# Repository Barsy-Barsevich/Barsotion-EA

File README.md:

# Barsotion GBK EpsilonAnomalain
Board computer for model rockets, the 10th board after Berkut

## ⚡️Manual
- [EA&TA_user_manual_revD.pdf (newest revision)](https://github.com/Barsy-Barsevich/Barsotion-TA/blob/main/Manual/EA%26TA_user_manual_revD.pdf)
- [EA&TA_user_manual_revC.pdf](https://github.com/Barsy-Barsevich/Barsotion-TA/blob/main/Manual/EA&TA_user_manual_revC.pdf)
- [EA&TA_user_manual_preliminary_edition_revB.pdf](https://github.com/Barsy-Barsevich/Barsotion-TA/blob/main/Manual/EA&TA_user_manual_preliminary_edition_revB.pdf)
- [EA&TA_user_manual_preliminary_edition_revA.pdf](https://github.com/Barsy-Barsevich/Barsotion-TA/blob/main/Manual/EA&TA_user_manual_preliminary_edition_revA.pdf)

## ⚡️Software
- [EA/TA software packet](https://github.com/Barsy-Barsevich/Barsotion-xA-software)

## ⚡️Continious progress
- [Previous version: Barsotion GBK DeltaAnomalain](https://github.com/Barsy-Barsevich/Barsotion-GBK-DeltaAnomalain)
- [Next version: Barsotion-TA (ThetaAnomalain)](https://github.com/Barsy-Barsevich/Barsotion-TA)

## ⚡️Schematic

## ⚡️Parameters
- Microcontroller: ESP32-S3FN8 (2x Xtensa LX7 core)
- Clock frequency: 240MHz
- Gyroscope: on-board ICM-42688-P (SPI, interrupt channel)
- Barometer: on-board, BMP388 (I2C)
- Hygrometer: on-board, AHT20 (I2C)
- Memory: 1Gbit SPI NAND Flash W25N04GVZEIG (Quad SPI)

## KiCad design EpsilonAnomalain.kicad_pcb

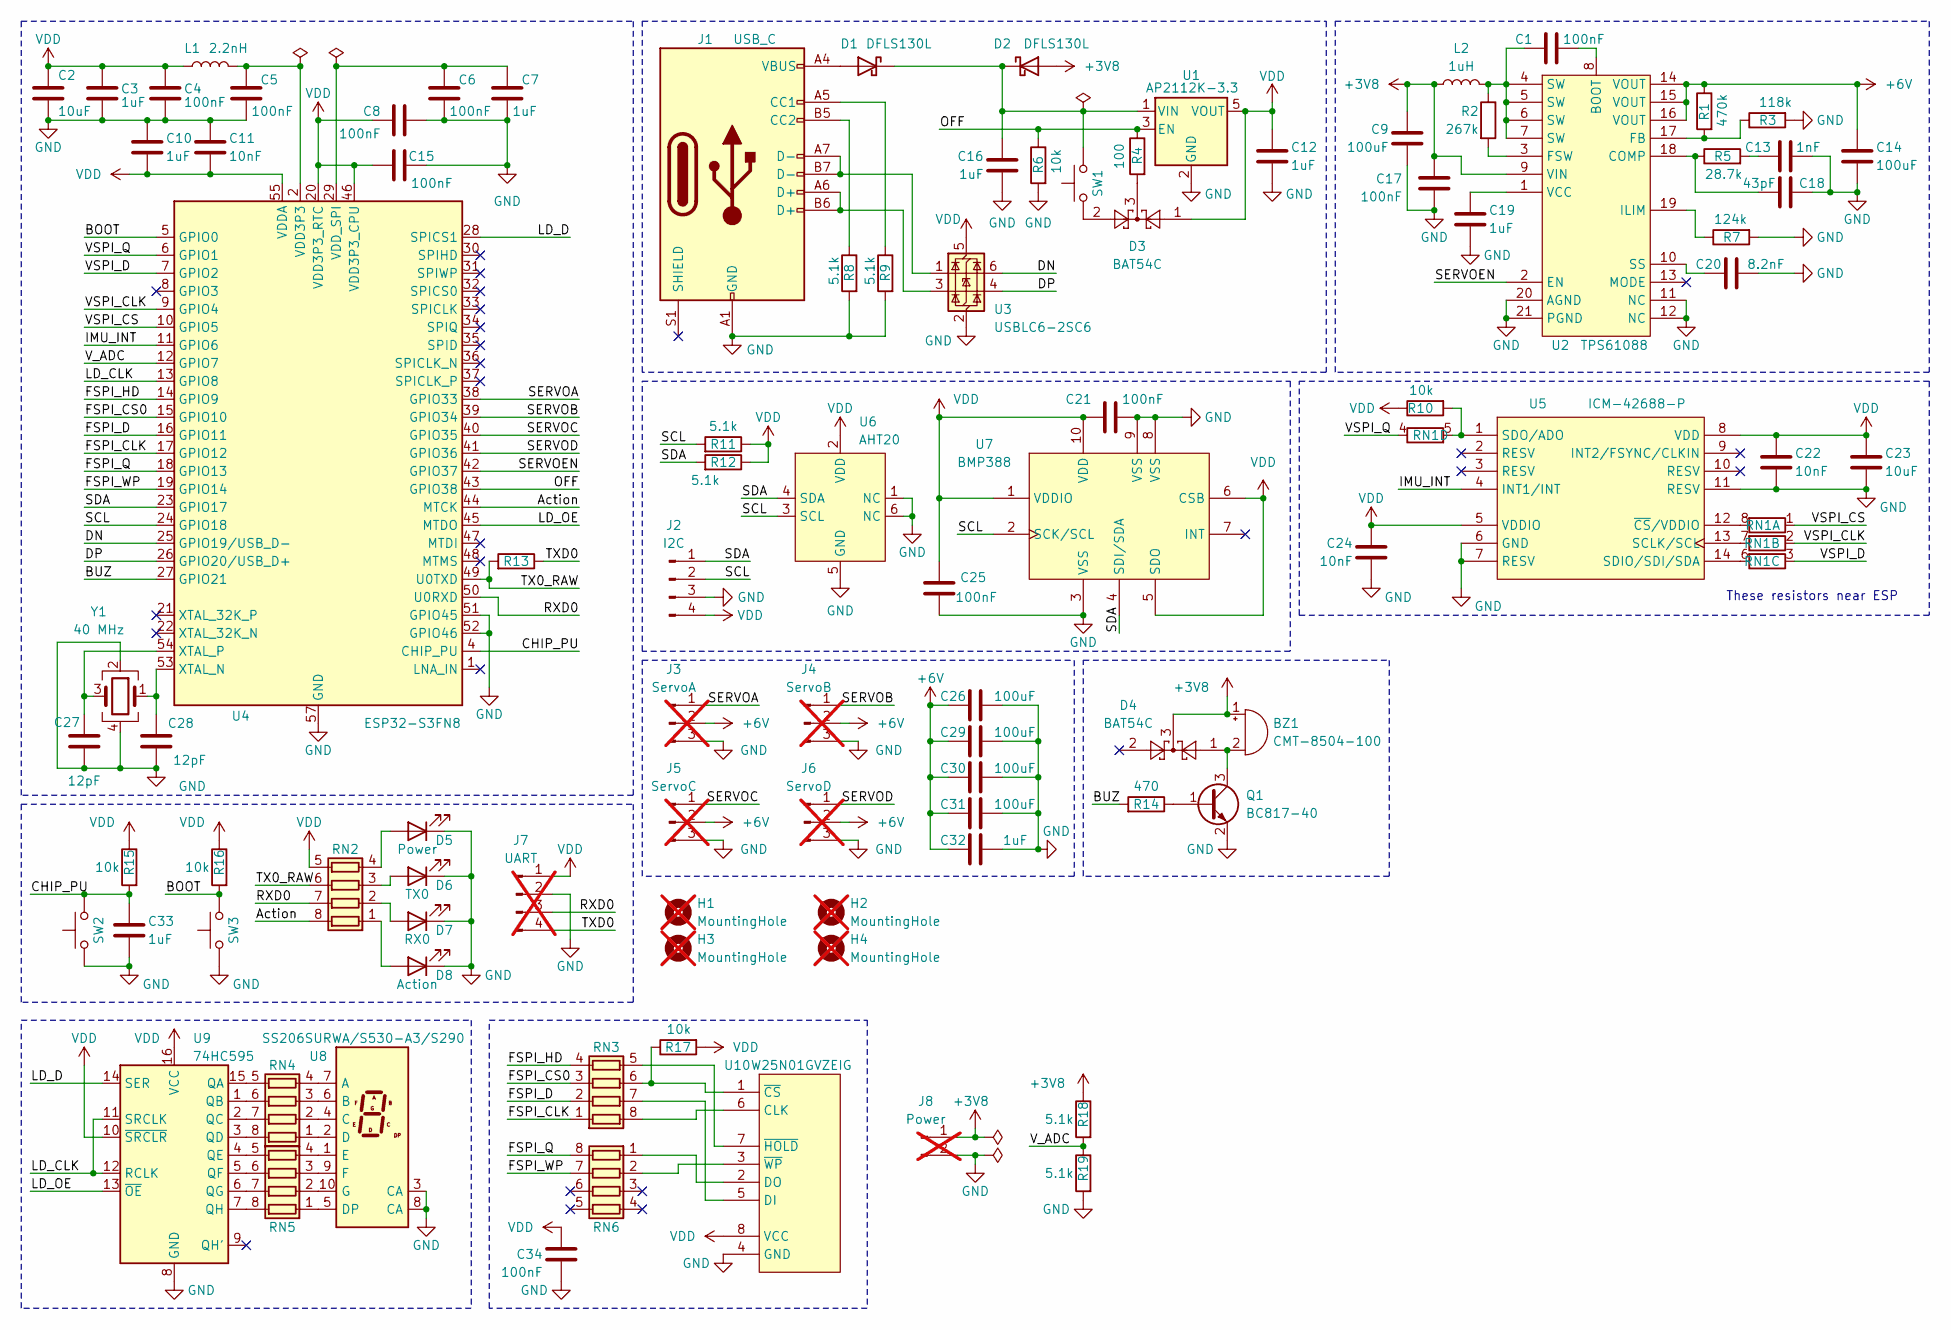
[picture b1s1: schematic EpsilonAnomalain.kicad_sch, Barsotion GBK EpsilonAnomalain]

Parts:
BZ1: CMT-8504-100; MagneticBuzzer_CUI_CMT-8504-100-SMT; Mfr.Part CMT-8504-100
C1, C4, C5, C6, C8, C15, C17, C21, C25, C34: 100nF; C_0402_1005Metric
C2, C23: 10uF; C_0402_1005Metric
C3, C7, C10, C12, C16, C19, C32, C33: 1uF; C_0402_1005Metric
C9, C14, C26, C29, C30, C31: 100uF; C_1206_3216Metric
C11, C22, C24: 10nF; C_0402_1005Metric
C13: 1nF; C_0402_1005Metric
C18: 43pF; C_0402_1005Metric
C20: 8.2nF; C_0402_1005Metric
C27, C28: 12pF; C_0402_1005Metric
D1, D2: DFLS130L; D_PowerDI-123
D3, D4: BAT54C; SOT-23
D5: Power; LED_0603_1608Metric
D6: TX0; LED_0603_1608Metric
D7: RX0; LED_0603_1608Metric
D8: Action; LED_0603_1608Metric
H1, H2, H3, H4: MountingHole; MountingHole_3.2mm_M3_Pad_Via; not fitted
J1: USB_C; USB_C_Receptacle_GCT_USB4105-xx-A_16P_TopMnt_Horizontal; Mfr.Part TYPE C-DB-116PWB
J2: I2C; JST_GH_SM04B-GHS-TB_1x04-1MP_P1.25mm_Horizontal; Mfr.Part A1257WR-S-4P
J3: ServoA; JST_XH_B3B-XH-A_1x03_P2.50mm_Vertical; not fitted
J4: ServoB; JST_XH_B3B-XH-A_1x03_P2.50mm_Vertical; not fitted
J5: ServoC; JST_XH_B3B-XH-A_1x03_P2.50mm_Vertical; not fitted
J6: ServoD; JST_XH_B3B-XH-A_1x03_P2.50mm_Vertical; not fitted
J7: UART; JST_XH_B4B-XH-A_1x04_P2.50mm_Vertical; not fitted
J8: Power; Battery_3V7_Cable_connector_v2; not fitted
L1: 2.2nH; L_0402_1005Metric
L2: 1uH; L_APV_APH0630; Mfr.Part APH0630T1R0M
Q1: BC817-40; SOT-23
R1: 470k; R_0402_1005Metric
R2: 267k; R_0402_1005Metric
R3: 118k; R_0402_1005Metric
R4: 100; R_0402_1005Metric
R5: 28.7k; R_0402_1005Metric
R6, R10, R15, R16, R17: 10k; R_0402_1005Metric
R7: 124k; R_0402_1005Metric
R8, R9, R11, R12, R18, R19: 5.1k; R_0402_1005Metric
R13, R14: 470; R_0402_1005Metric
RN1: 47; R_Array_Convex_4x0402
RN2, RN4, RN5: 1k; R_Array_Convex_4x0402
RN3, RN6: 0; R_Array_Convex_4x0402
SW1, SW2, SW3: TS-1187A-B-A-B; SW_SPST_TL3342; Mfr.Part TS-1187A-B-A-B
U1: AP2112K-3.3; SOT-23-5; Mfr.Part AP2112K-3.3
U2: TPS61088; RHL0020A; Mfr.Part TPS61088
U3: USBLC6-2SC6; SOT-23-6; Mfr.Part USBLC6-2SC6
U4: ESP32-S3FN8; QFN-56-1EP_7x7mm_P0.4mm_EP4x4mm; Mfr.Part ESP32-S3FN8
U5: ICM-42688-P; LGA-14_3x2.5mm_P0.5mm_LayoutBorder3x4y; Mfr.Part ICM-42688-P
U6: AHT20; Mfr.Part AHT20
U7: BMP388; BMP388_v2; Mfr.Part BMP388
U8: SS206SURWA/S530-A3/S290; SS206SURWA; Mfr.Part SS206SURWA/S530-A3/S290
U9: 74HC595; TSSOP-16_4.4x5mm_P0.65mm
U10: W25N01GVZEIG; WSON-8-1EP_8x6mm_P1.27mm_EP3.4x4.3mm; Mfr.Part W25N01GVZEIG
Y1: 40 MHz; Crystal_SMD_3225-4Pin_3.2x2.5mm

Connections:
+3V8: BZ1.1 (+), C9.1, C17.1, D2.2 (A), D4.3, J8.1, L2.1, R18.1, U2.9 (VIN)
+6V: C14.1, C26.1, C29.1, C30.1, C31.1, C32.1, J3.2, J4.2, J5.2, J6.2, R1.1, U2.14 (VOUT), U2.15 (VOUT), U2.16 (VOUT)
/Action: RN2.8 (R1.2), U4.44 (MTCK)
/BOOT: R16.2, SW3.2, U4.5 (GPIO0)
/BUZ: R14.2, U4.27 (GPIO21)
/CHIP_PU: C33.1, R15.2, SW2.2, U4.4 (CHIP_PU)
/DN: U3.6 (I/O1), U4.25 (GPIO19/USB_D-)
/DP: U3.4 (I/O2), U4.26 (GPIO20/USB_D+)
/FSPI_CLK: RN3.1 (R1.1), U4.17 (GPIO12)
/FSPI_CS0: RN3.3 (R3.1), U4.15 (GPIO10)
/FSPI_D: RN3.2 (R2.1), U4.16 (GPIO11)
/FSPI_HD: RN3.4 (R4.1), U4.14 (GPIO9)
/FSPI_Q: RN6.8 (R1.2), U4.18 (GPIO13)
/FSPI_WP: RN6.7 (R2.2), U4.19 (GPIO14)
/IMU_INT: U4.11 (GPIO6), U5.4 (INT1/INT)
/LD_CLK: U4.13 (GPIO8), U9.11 (SRCLK), U9.12 (RCLK)
/LD_D: U4.28 (SPICS1), U9.14 (SER)
/LD_OE: U4.45 (MTDO), U9.13 (~OE)
/OFF: R4.1, R6.1, U1.3 (EN), U4.43 (GPIO38)
/RXD0: J7.3, RN2.7 (R2.2), U4.50 (U0RXD)
/SCL: J2.2, R11.2, U4.24 (GPIO18), U6.3 (SCL), U7.2 (SCK/SCL)
/SDA: J2.1, R12.2, U4.23 (GPIO17), U6.4 (SDA), U7.4 (SDI/SDA)
/SERVOA: J3.1, U4.38 (GPIO33)
/SERVOB: J4.1, U4.39 (GPIO34)
/SERVOC: J5.1, U4.40 (GPIO35)
/SERVOD: J6.1, U4.41 (GPIO36)
/SERVOEN: U2.2 (EN), U4.42 (GPIO37)
/TX0_RAW: R13.2, RN2.6 (R3.2), U4.49 (U0TXD)
/TXD0: J7.4, R13.1
/VSPI_CLK: RN1.2 (R2.1), U4.9 (GPIO4)
/VSPI_CS: RN1.1 (R1.1), U4.10 (GPIO5)
/VSPI_D: RN1.3 (R3.1), U4.7 (GPIO2)
/VSPI_Q: RN1.4 (R4.1), U4.6 (GPIO1)
/V_ADC: R18.2, R19.1, U4.12 (GPIO7)
GND: C2.2, C3.2, C4.2, C5.2, C6.2, C7.2, C8.2, C9.2, C10.1, C11.1, C12.2, C13.1, C14.2, C15.2, C16.2, C17.2, C18.1, C19.2, C20.1, C21.2, C22.2, C23.2, C24.2, C25.1, C26.2, C27.2, C28.2, C29.2, C30.2, C31.2, C32.2, C33.2, C34.2, D5.1 (K), D6.1 (K), D7.1 (K), D8.1 (K), J1.A1 (GND), J1.A12 (GND), J1.B1 (GND), J1.B12 (GND), J2.3, J3.3, J4.3, J5.3, J6.3, J7.2, J8.2, Q1.2 (E), R3.2, R6.2, R7.2, R8.2, R9.2, R19.2, SW2.1, SW3.1, U1.2 (GND), U2.11 (NC), U2.12 (NC), U2.20 (AGND), U2.21 (PGND), U3.2 (GND), U4.51 (GPIO45), U4.52 (GPIO46), U4.57 (GND), U5.6 (GND), U5.7 (RESV), U5.11 (RESV), U6.1 (NC), U6.5 (GND), U6.6 (NC), U7.3 (VSS), U7.8 (VSS), U7.9 (VSS), U8.3 (CA), U8.8 (CA), U9.8 (GND), U10.4 (GND), Y1.2, Y1.4
unnamed: BZ1.2 (-), D4.1, Q1.3 (C)
unnamed: C1.2, L2.2, R2.1, U2.4 (SW), U2.5 (SW), U2.6 (SW), U2.7 (SW)
unnamed: C5.1, L1.2, U4.2 (VDD3P3), U4.3 (VDD3P3)
unnamed: C13.2, R5.2
unnamed: D1.2 (A), J1.A4 (VBUS), J1.A9 (VBUS), J1.B4 (VBUS), J1.B9 (VBUS)
unnamed: C16.1, D1.1 (K), D2.1 (K), SW1.2, U1.1 (VIN)
unnamed: D3.2, SW1.1
unnamed: D3.3, R4.2
unnamed: D5.2 (A), RN2.4 (R4.1)
unnamed: D6.2 (A), RN2.3 (R3.1)
unnamed: D7.2 (A), RN2.2 (R2.1)
unnamed: D8.2 (A), RN2.1 (R1.1)
unnamed: J1.A5 (CC1), R9.1
unnamed: J1.B5 (CC2), R8.1
unnamed: J1.A6 (D+), J1.B6 (D+), U3.3 (I/O2)
unnamed: J1.A7 (D-), J1.B7 (D-), U3.1 (I/O1)
unnamed: Q1.1 (B), R14.1
unnamed: RN1.8 (R1.2), U5.12 (~CS/VDDIO)
unnamed: RN1.7 (R2.2), U5.13 (SCLK/SCL)
unnamed: RN1.6 (R3.2), U5.14 (SDIO/SDI/SDA)
unnamed: R10.2, RN1.5 (R4.2), U5.1 (SDO/ADO)
unnamed: RN3.8 (R1.2), U10.6 (CLK)
unnamed: RN3.7 (R2.2), U10.5 (DI)
unnamed: R17.1, RN3.6 (R3.2), U10.1 (~CS)
unnamed: RN3.5 (R4.2), U10.7 (~HOLD)
unnamed: RN4.1 (R1.1), U8.2 (D)
unnamed: RN4.8 (R1.2), U9.3 (QD)
unnamed: RN4.2 (R2.1), U8.4 (C)
unnamed: RN4.7 (R2.2), U9.2 (QC)
unnamed: RN4.3 (R3.1), U8.6 (B)
unnamed: RN4.6 (R3.2), U9.1 (QB)
unnamed: RN4.4 (R4.1), U8.7 (A)
unnamed: RN4.5 (R4.2), U9.15 (QA)
unnamed: RN5.1 (R1.1), U8.5 (DP)
unnamed: RN5.8 (R1.2), U9.7 (QH)
unnamed: RN5.2 (R2.1), U8.10 (G)
unnamed: RN5.7 (R2.2), U9.6 (QG)
unnamed: RN5.3 (R3.1), U8.9 (F)
unnamed: RN5.6 (R3.2), U9.5 (QF)
unnamed: RN5.4 (R4.1), U8.1 (E)
unnamed: RN5.5 (R4.2), U9.4 (QE)
unnamed: RN6.1 (R1.1), U10.2 (DO)
unnamed: RN6.2 (R2.1), U10.3 (~WP)
unnamed: C1.1, U2.8 (BOOT)
unnamed: C18.2, R5.1, U2.18 (COMP)
unnamed: R1.2, R3.1, U2.17 (FB)
unnamed: R2.2, U2.3 (FSW)
unnamed: R7.1, U2.19 (ILIM)
unnamed: C20.2, U2.10 (SS)
unnamed: C19.1, U2.1 (VCC)
unnamed: C6.1, C7.1, U4.29 (VDD_SPI)
unnamed: C28.1, U4.53 (XTAL_N), Y1.1
unnamed: C27.1, U4.54 (XTAL_P), Y1.3
VDD: C2.1, C3.1, C4.1, C8.1, C10.2, C11.2, C12.1, C15.1, C21.1, C22.1, C23.1, C24.1, C25.2, C34.1, D3.1, J2.4, J7.1, L1.1, R10.1, R11.1, R12.1, R15.1, R16.1, R17.2, RN2.5 (R4.2), U1.5 (VOUT), U3.5 (VBUS), U4.20 (VDD3P3_RTC), U4.46 (VDD3P3_CPU), U4.55 (VDDA), U4.56 (VDDA), U5.5 (VDDIO), U5.8 (VDD), U6.2 (VDD), U7.1 (VDDIO), U7.5 (SDO), U7.6 (CSB), U7.10 (VDD), U9.10 (~SRCLR), U9.16 (VCC), U10.8 (VCC)

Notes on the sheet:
These resistors near ESP

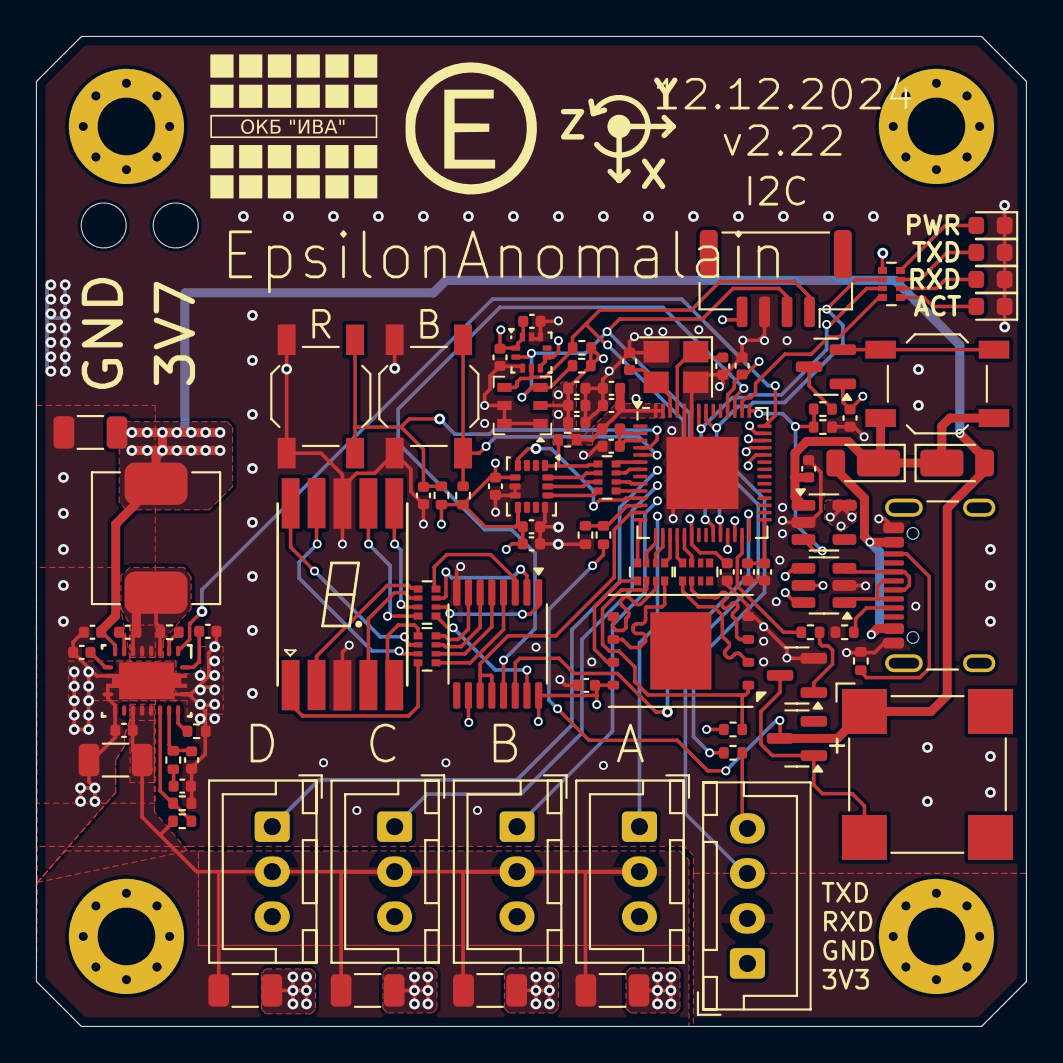
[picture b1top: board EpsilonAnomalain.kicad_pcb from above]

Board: 4 copper layers, 55.0 x 55.0 mm, 97 parts (0 on the bottom side), 89 nets.

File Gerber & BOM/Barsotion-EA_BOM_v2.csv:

Reference,Value,Datasheet,Footprint,Qty,DNP,Description,Mfr.Part
BZ1,CMT-8504-100,https://www.lcsc.com/datasheet/lcsc_datasheet_2410010302_Mur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,Buzzer_Beeper:MagneticBuzzer_CUI_CMT-8504-100-SMT,1,,"Buzzer, polarized",CMT-8504-100
"C1,C4,C5,C6,C8,C15,C17,C21,C25,C34",100nF,~,Capacitor_SMD:C_0402_1005Metric,10,,Unpolarized capacitor,
"C2,C23",10uF,~,Capacitor_SMD:C_0402_1005Metric,2,,Unpolarized capacitor,
"C3,C7,C10,C12,C16,C19,C32,C33",1uF,~,Capacitor_SMD:C_0402_1005Metric,8,,Unpolarized capacitor,
"C9,C14,C26,C29,C30,C31",100uF,~,Capacitor_SMD:C_1206_3216Metric,6,,Unpolarized capacitor,
"C11,C22,C24",10nF,~,Capacitor_SMD:C_0402_1005Metric,3,,Unpolarized capacitor,
C13,1nF,~,Capacitor_SMD:C_0402_1005Metric,1,,Unpolarized capacitor,
C18,43pF,~,Capacitor_SMD:C_0402_1005Metric,1,,Unpolarized capacitor,
C20,8.2nF,~,Capacitor_SMD:C_0402_1005Metric,1,,Unpolarized capacitor,
"C27,C28",12pF,~,Capacitor_SMD:C_0402_1005Metric,2,,Unpolarized capacitor,
"D1,D2",DFLS130L,~,Diode_SMD:D_PowerDI-123,2,,Schottky diode,
"D3,D4",BAT54C,http://www.diodes.com/_files/datasheets/ds11005.pdf,Package_TO_SOT_SMD:SOT-23,2,,"dual schottky barrier diode, common cathode",
D5,Power,~,LED_SMD:LED_0603_1608Metric,1,,Yellow Light emitting diode,
D6,TX0,~,LED_SMD:LED_0603_1608Metric,1,,Yellow Light emitting diode,
D7,RX0,~,LED_SMD:LED_0603_1608Metric,1,,Yellow Light emitting diode,
D8,Action,~,LED_SMD:LED_0603_1608Metric,1,,Yellow Light emitting diode,
J1,USB_C,https://www.usb.org/sites/default/files/documents/usb_type-c.zip,Connector_USB:USB_C_Receptacle_GCT_USB4105-xx-A_16P_TopMnt_Horizontal,1,,"USB 2.0-only 16P Type-C Receptacle connector, mfr part TYPE C-DB-116PWB",TYPE C-DB-116PWB
J2,I2C,~,Connector_JST:JST_GH_SM04B-GHS-TB_1x04-1MP_P1.25mm_Horizontal,1,,"Generic connector, single row, 01x04, script generated",A1257WR-S-4P
L1,2.2nH,https://www.lcsc.com/datasheet/lcsc_datasheet_2409302232_APV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,Inductor_SMD:L_0402_1005Metric,1,,Inductor,
L2,1uH,https://www.lcsc.com/datasheet/lcsc_datasheet_2409302232_APV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,Inductor_SMD:L_APV_APH0630,1,,Power inductor,APH0630T1R0M
Q1,BC817-40,https://www.onsemi.com/pub/Collateral/BC818-D.pdf,Package_TO_SOT_SMD:SOT-23,1,,"0.8A Ic, 45V Vce, NPN Transistor, SOT-23",
R1,470k,~,Resistor_SMD:R_0402_1005Metric,1,,Resistor,
R2,267k,~,Resistor_SMD:R_0402_1005Metric,1,,Resistor,
R3,118k,~,Resistor_SMD:R_0402_1005Metric,1,,Resistor,
R4,100,~,Resistor_SMD:R_0402_1005Metric,1,,Resistor,
R5,28.7k,~,Resistor_SMD:R_0402_1005Metric,1,,Resistor,
"R6,R10,R15,R16,R17",10k,~,Resistor_SMD:R_0402_1005Metric,5,,Resistor,
R7,124k,~,Resistor_SMD:R_0402_1005Metric,1,,Resistor,
"R8,R9,R11,R12,R18,R19",5.1k,~,Resistor_SMD:R_0402_1005Metric,6,,Resistor,
"R13,R14",470,~,Resistor_SMD:R_0402_1005Metric,2,,Resistor,
RN1,47,~,Resistor_SMD:R_Array_Convex_4x0402,1,,"4 resistor network, parallel topology, split",
"RN2,RN4,RN5",1k,~,Resistor_SMD:R_Array_Convex_4x0402,3,,"4 resistor network, parallel topology",
"RN3,RN6",0,~,Resistor_SMD:R_Array_Convex_4x0402,2,,"4 resistor network, parallel topology",
"SW1,SW2,SW3",TS-1187A-B-A-B,~,Button_Switch_SMD:SW_SPST_TL3342,3,,TS-1187A-B-A-B,TS-1187A-B-A-B
U1,AP2112K-3.3,https://www.diodes.com/assets/Datasheets/AP2112.pdf,Package_TO_SOT_SMD:SOT-23-5,1,,"600mA low dropout linear regulator, with enable pin, 3.8V-6V input voltage range, 3.3V fixed positive output, SOT-23-5",AP2112K-3.3
U2,TPS61088,,UltraLibrarian:RHL0020A,1,,Texas Instruments DC-DC Pullup converter,TPS61088
U3,USBLC6-2SC6,https://www.st.com/resource/en/datasheet/usblc6-2.pdf,Package_TO_SOT_SMD:SOT-23-6,1,,"Very low capacitance ESD protection diode, 2 data-line, SOT-23-6",USBLC6-2SC6
U4,ESP32-S3FN8,https://www.espressif.com/sites/default/files/documentation/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,Package_DFN_QFN:QFN-56-1EP_7x7mm_P0.4mm_EP4x4mm,1,,"Microcontroller, Wi-Fi 802.11b/g/n, Bluetooth, 32bit",ESP32-S3FN8
U5,ICM-42688-P,https://invensense.tdk.com/wp-content/uploads/2020/04/ds-000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,Package_LGA:LGA-14_3x2.5mm_P0.5mm_LayoutBorder3x4y,1,,InvenSense High-precision 6-axes gyroscope accelerometer,ICM-42688-P
U6,AHT20,https://files.seeedstudio.com/wiki/Grove-AHT20_I2C_Industria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,CustomPackage:AHT20,1,,Digital hygrometer,AHT20
U7,BMP388,https://pdf1.alldatasheet.com/datasheet-pdf/download/1132070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,CustomPackage:BMP388,1,,Bosch barometer thermometer,BMP388
U8,SS206SURWA/S530-A3/S290,https://www.lcsc.com/datasheet/lcsc_datasheet_2409302134_Eve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,CustomPackage:SS206SURWA,1,,"One digit 7 segment hyper red LED, common anode",SS206SURWA/S530-A3/S290
U9,74HC595,http://www.ti.com/lit/ds/symlink/sn74hc595.pdf,Package_SO:TSSOP-16_4.4x5mm_P0.65mm,1,,8-bit serial in/out Shift Register 3-State Outputs,
U10,W25N01GVZEIG,https://www.lcsc.com/datasheet/lcsc_datasheet_2304140030_Win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,Package_SON:WSON-8-1EP_8x6mm_P1.27mm_EP3.4x4.3mm,1,,SPI NAND Flash 1Gbit chip,W25N01GVZEIG
Y1,40 MHz,~,Crystal:Crystal_SMD_3225-4Pin_3.2x2.5mm,1,,"Four pin crystal, GND on pins 2 and 4",

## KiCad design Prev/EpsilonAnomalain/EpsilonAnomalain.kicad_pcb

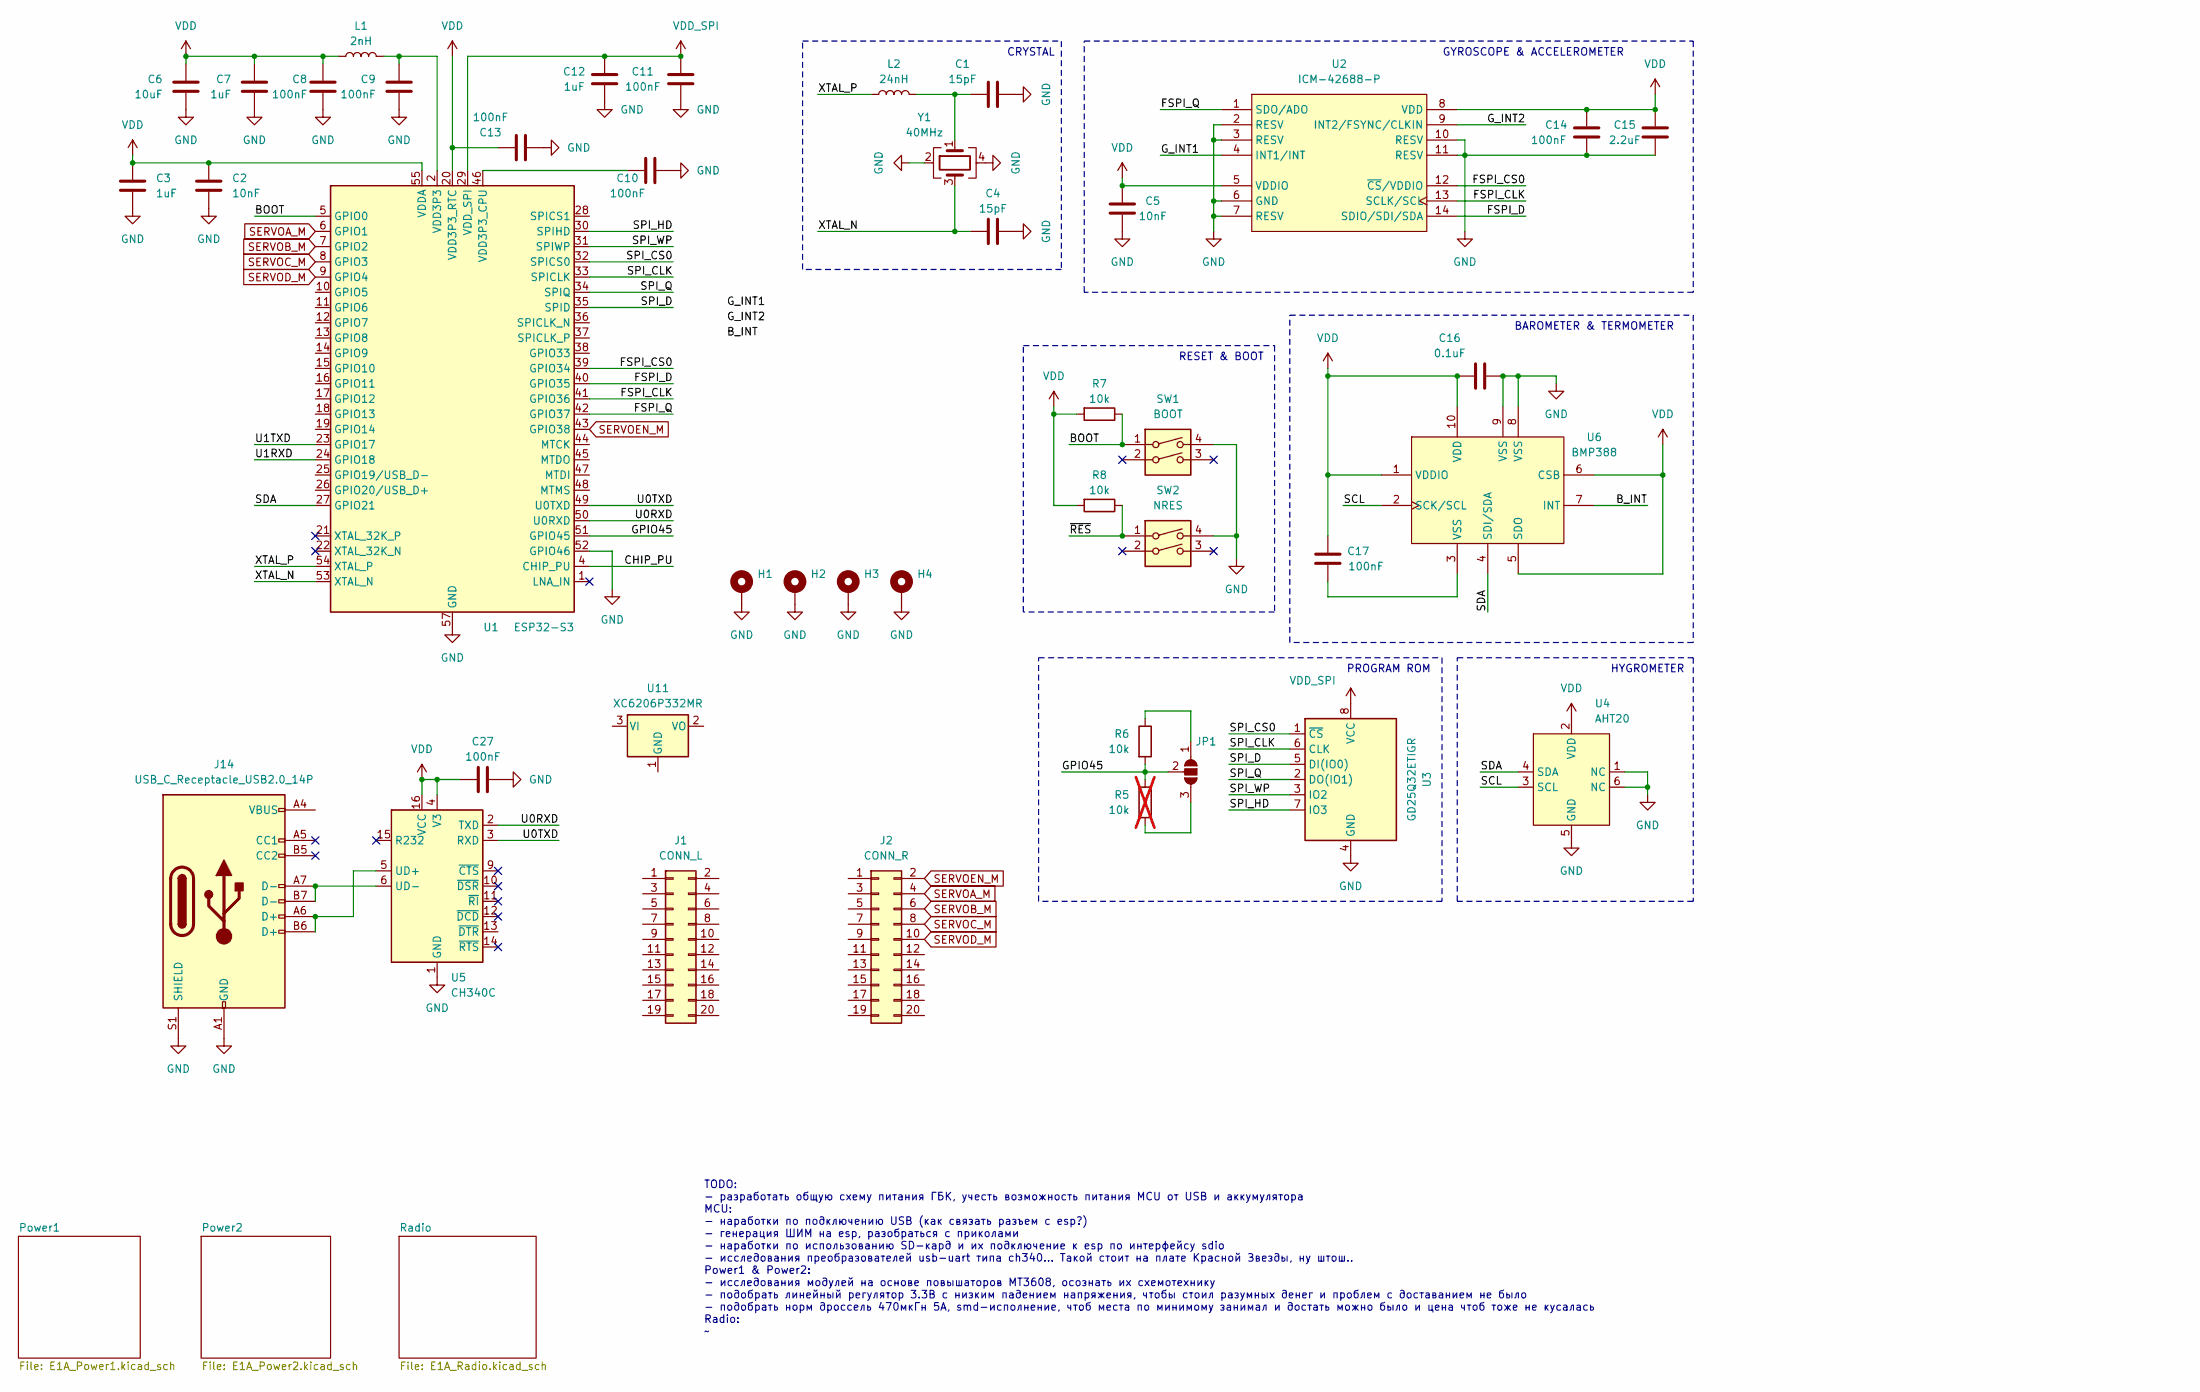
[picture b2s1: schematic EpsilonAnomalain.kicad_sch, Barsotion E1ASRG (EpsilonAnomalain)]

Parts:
C1, C4: 15pF; C_0402_1005Metric
C2, C5: 10nF; C_0402_1005Metric
C3, C7, C12: 1uF; C_0402_1005Metric
C6: 10uF; C_0402_1005Metric
C8, C9, C10, C11, C13, C14, C17, C27: 100nF; C_0402_1005Metric
C15: 2.2uF; C_0402_1005Metric
C16: 0.1uF; C_0402_1005Metric
H1, H2, H3, H4: MountingHole_Pad; MountingHole_3.2mm_M3_Pad_Via
J1: CONN_L; PinSocket_2x10_P2.54mm_Vertical_SMD
J2: CONN_R; PinSocket_2x10_P2.54mm_Vertical_SMD
J14: USB_C_Receptacle_USB2.0_14P; USB_C_Receptacle_GCT_USB4105-xx-A_16P_TopMnt_Horizontal
JP1: Flash_Supply; SolderJumper-3_P1.3mm_Open_RoundedPad1.0x1.5mm_NumberLabels
L1: 2nH; L_0402_1005Metric
L2: 24nH; L_0402_1005Metric
R5: 10k; R_0402_1005Metric; not fitted
R6, R7, R8: 10k; R_0402_1005Metric
SW1: BOOT; SW_Push_1P1T_XKB_TS-1187A
SW2: NRES; SW_Push_1P1T_XKB_TS-1187A
U1: ESP32-S3; QFN-56-1EP_7x7mm_P0.4mm_EP4x4mm
U2: ICM-42688-P; LGA-14_3x2.5mm_P0.5mm_LayoutBorder3x4y
U3: GD25Q32ETIGR; SOP-8_3.9x4.9mm_P1.27mm
U4: AHT20
U5: CH340C; SOIC-16_3.9x9.9mm_P1.27mm
U6: BMP388; ST_HLGA-10_2x2mm_P0.5mm_LayoutBorder3x2y
U11: XC6206P332MR; SOT-23-3
Y1: 40MHz; Crystal_SMD_3225-4Pin_3.2x2.5mm

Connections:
/BOOT: R7.1, SW1.1, U1.5 (GPIO0)
/B_INT: U6.7 (INT)
/CHIP_PU: U1.4 (CHIP_PU)
/FSPI_CLK: U1.41 (GPIO36), U2.13 (SCLK/SCL)
/FSPI_CS0: U1.39 (GPIO34), U2.12 (~CS/VDDIO)
/FSPI_D: U1.40 (GPIO35), U2.14 (SDIO/SDI/SDA)
/FSPI_Q: U1.42 (GPIO37), U2.1 (SDO/ADO)
/GPIO45: JP1.2 (C), R5.1, R6.2, U1.51 (GPIO45)
/G_INT1: U2.4 (INT1/INT)
/G_INT2: U2.9 (INT2/FSYNC/CLKIN)
/SCL: U4.3 (SCL), U6.2 (SCK/SCL)
/SDA: U1.27 (GPIO21), U4.4 (SDA), U6.4 (SDI/SDA)
/SPI_CLK: U1.33 (SPICLK), U3.6 (CLK)
/SPI_CS0: U1.32 (SPICS0), U3.1 (~CS)
/SPI_D: U1.35 (SPID), U3.5 (DI(IO0))
/SPI_HD: U1.30 (SPIHD), U3.7 (IO3)
/SPI_Q: U1.34 (SPIQ), U3.2 (DO(IO1))
/SPI_WP: U1.31 (SPIWP), U3.3 (IO2)
/U0RXD: U1.50 (U0RXD), U5.2 (TXD)
/U0TXD: U1.49 (U0TXD), U5.3 (RXD)
/U1RXD: U1.24 (GPIO18)
/U1TXD: U1.23 (GPIO17)
/XTAL_N: C4.2, U1.53 (XTAL_N), Y1.3
/XTAL_P: L2.1, U1.54 (XTAL_P)
/~RES: R8.1, SW2.1
GND: C1.1, C2.2, C3.2, C4.1, C5.2, C6.2, C7.2, C8.2, C9.2, C10.2, C11.2, C12.1, C13.2, C14.2, C15.2, C16.2, C27.1, H1.1, H2.1, H3.1, H4.1, J14.A1 (GND), J14.A12 (GND), J14.B1 (GND), J14.B12 (GND), J14.S1 (SHIELD), SW1.4, SW2.4, U1.52 (GPIO46), U1.57 (GND), U2.2 (RESV), U2.3 (RESV), U2.6 (GND), U2.7 (RESV), U2.10 (RESV), U2.11 (RESV), U3.4 (GND), U4.1 (NC), U4.5 (GND), U4.6 (NC), U5.1 (GND), U6.8 (VSS), U6.9 (VSS), Y1.2, Y1.4; also elsewhere on the board
unnamed: C1.2, L2.2, Y1.1
unnamed: C9.1, L1.2, U1.2 (VDD3P3), U1.3 (VDD3P3)
unnamed: C17.2, U6.3 (VSS)
unnamed: J14.A4 (VBUS), J14.A9 (VBUS), J14.B4 (VBUS), J14.B9 (VBUS)
unnamed: JP1.1 (A), R6.1
unnamed: JP1.3 (B), R5.2
unnamed: C10.1, U1.46 (VDD3P3_CPU)
unnamed: J14.A6 (D+), J14.B6 (D+), U5.5 (UD+)
unnamed: J14.A7 (D-), J14.B7 (D-), U5.6 (UD-)
SERVOA_M: J2.4, U1.6 (GPIO1)
SERVOB_M: J2.6, U1.7 (GPIO2)
SERVOC_M: J2.8, U1.8 (GPIO3)
SERVOD_M: J2.10, U1.9 (GPIO4)
SERVOEN_M: J2.2, U1.43 (GPIO38)
VDD_SPI: C11.1, C12.2, U1.29 (VDD_SPI), U3.8 (VCC)

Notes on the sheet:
GYROSCOPE & ACCELEROMETER
CRYSTAL
PROGRAM ROM
HYGROMETER
BAROMETER & TERMOMETER
RESET & BOOT
TODO: - разработать общую схему питания ГБК, учесть возможность питания MCU от USB и аккумулятора MCU: - наработки по подключению USB (как связать разъем с esp?) - генерация ШИМ на esp, разобраться с приколами - наработки по использованию SD-кард и их подключение к esp по интерфейсу sdio - исследов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

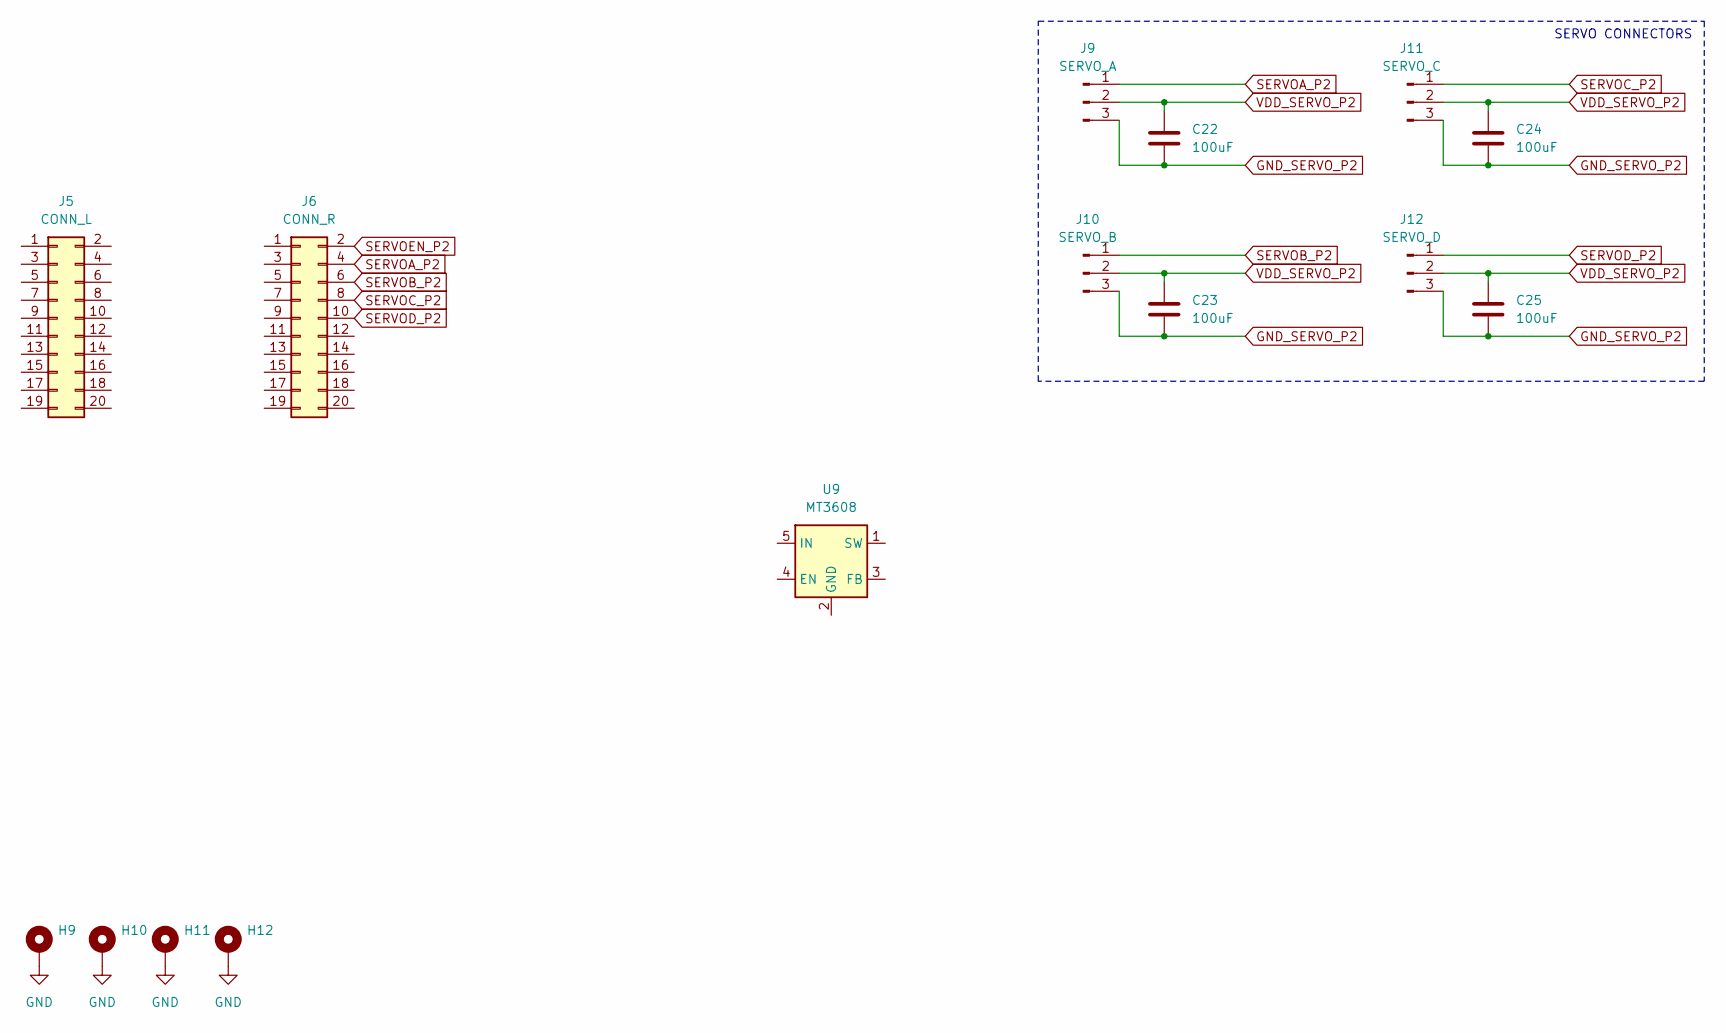
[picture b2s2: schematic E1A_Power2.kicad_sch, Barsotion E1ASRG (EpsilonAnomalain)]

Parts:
C22, C23, C24, C25: 100uF; C_1206_3216Metric
H9, H10, H11, H12: MountingHole_Pad; MountingHole_3.2mm_M3_Pad_Via
J5: CONN_L; PinSocket_2x10_P2.54mm_Vertical_SMD
J6: CONN_R; PinSocket_2x10_P2.54mm_Vertical_SMD
J9: SERVO_A; JST_EH_S3B-EH_1x03_P2.50mm_Horizontal
J10: SERVO_B; JST_EH_S3B-EH_1x03_P2.50mm_Horizontal
J11: SERVO_C; JST_EH_S3B-EH_1x03_P2.50mm_Horizontal
J12: SERVO_D; JST_EH_S3B-EH_1x03_P2.50mm_Horizontal
U9: MT3608; SOT-23-6

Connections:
GND: H9.1, H10.1, H11.1, H12.1; also elsewhere on the board
GND_SERVO_P2: C22.2, C23.2, C24.2, C25.2, J9.3, J10.3, J11.3, J12.3
SERVOA_P2: J6.4, J9.1
SERVOB_P2: J6.6, J10.1
SERVOC_P2: J6.8, J11.1
SERVOD_P2: J6.10, J12.1
SERVOEN_P2: J6.2
VDD_SERVO_P2: C22.1, C23.1, C24.1, C25.1, J9.2, J10.2, J11.2, J12.2

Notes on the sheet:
SERVO CONNECTORS

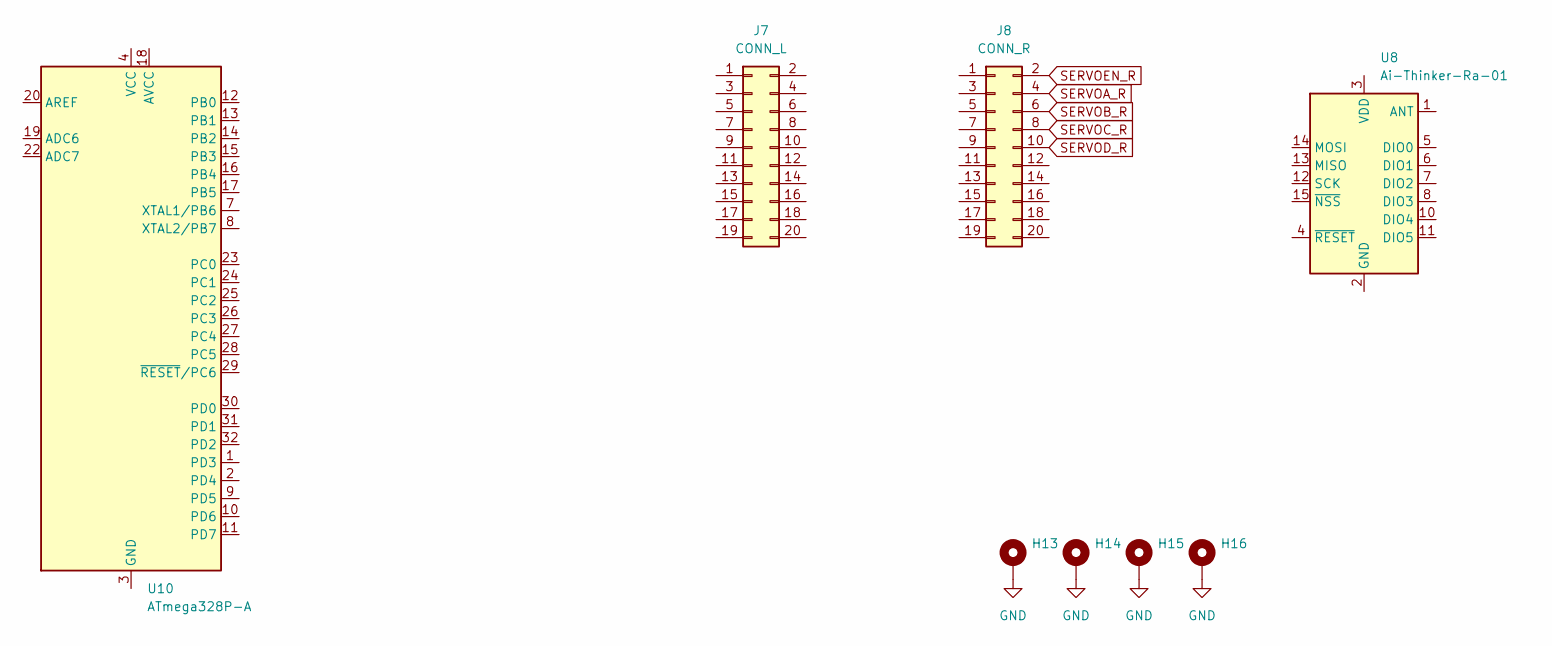
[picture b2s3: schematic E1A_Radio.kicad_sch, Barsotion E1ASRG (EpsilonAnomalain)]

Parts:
H13, H14, H15, H16: MountingHole_Pad; MountingHole_3.2mm_M3_Pad_Via
J7: CONN_L; PinSocket_2x10_P2.54mm_Vertical_SMD
J8: CONN_R; PinSocket_2x10_P2.54mm_Vertical_SMD
U8: Ai-Thinker-Ra-01; Ai-Thinker-Ra-01-LoRa
U10: ATmega328P-A; TQFP-32_7x7mm_P0.8mm

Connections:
GND: H13.1, H14.1, H15.1, H16.1; also elsewhere on the board
unnamed: U8.2 (GND), U8.9 (GND), U8.16 (GND)
unnamed: U10.3 (GND), U10.5 (GND), U10.21 (GND)
unnamed: U10.4 (VCC), U10.6 (VCC)
SERVOA_R: J8.4
SERVOB_R: J8.6
SERVOC_R: J8.8
SERVOD_R: J8.10
SERVOEN_R: J8.2

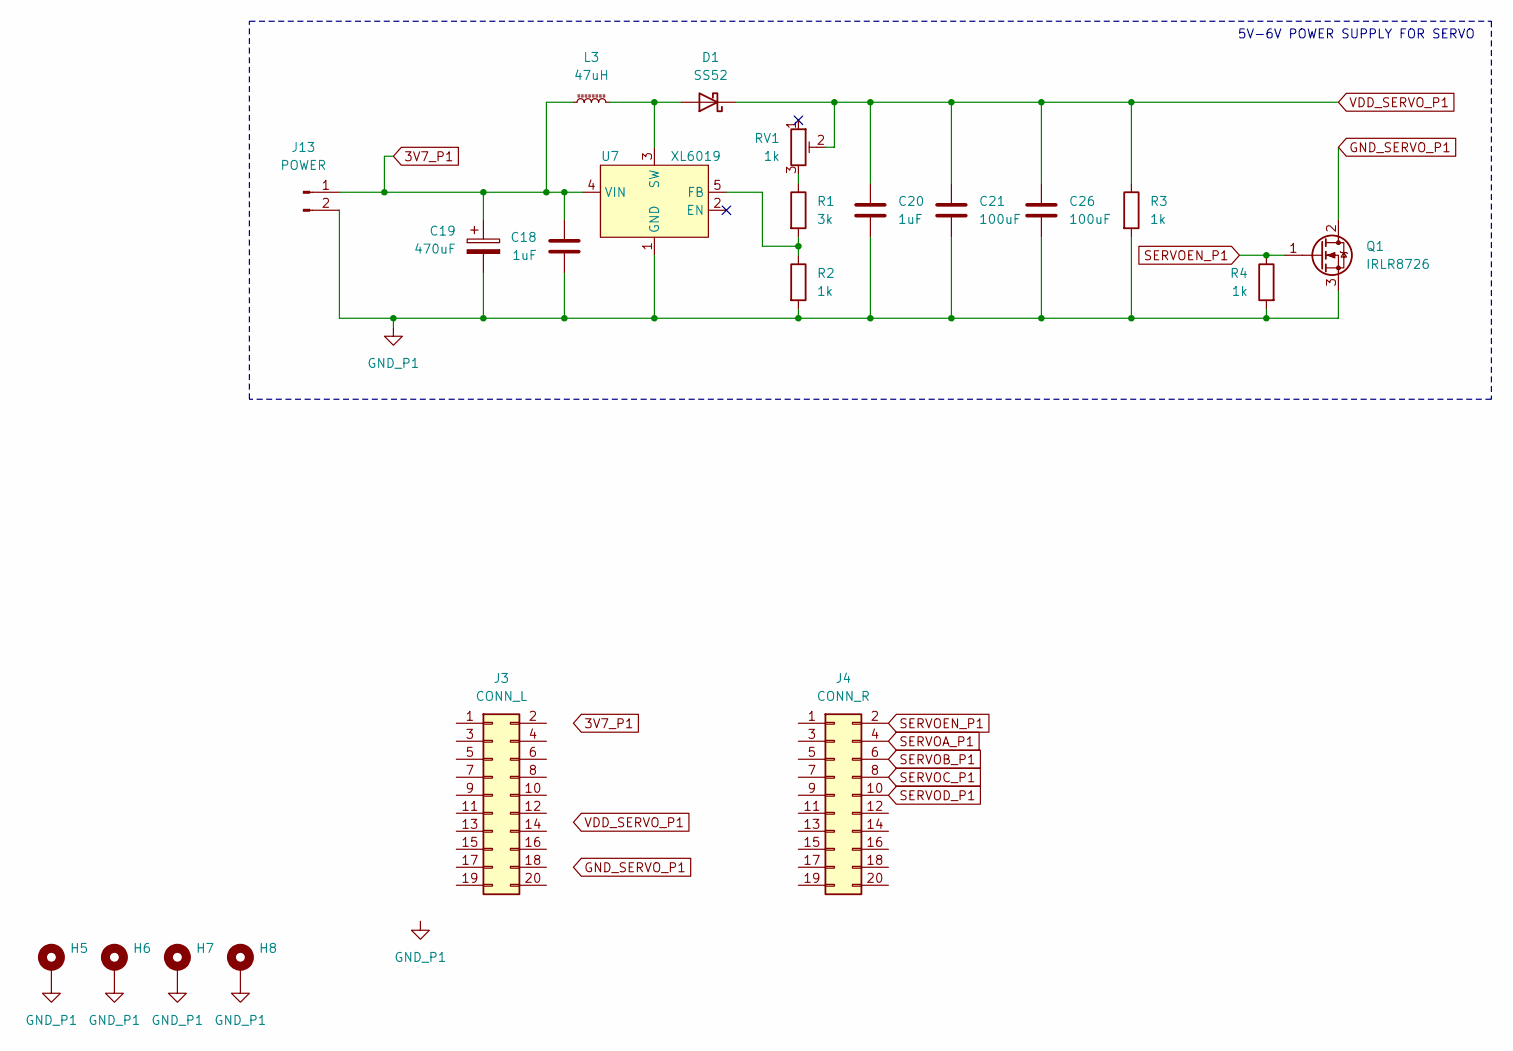
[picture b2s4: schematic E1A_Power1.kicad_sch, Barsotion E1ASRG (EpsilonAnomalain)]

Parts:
C18, C20: 1uF; C_0402_1005Metric
C19: 470uF
C21, C26: 100uF; C_1206_3216Metric
D1: SS52; D_SMA
H5, H6, H7, H8: MountingHole_Pad; MountingHole_3.2mm_M3_Pad_Via
J3: CONN_L; PinSocket_2x10_P2.54mm_Vertical_SMD
J4: CONN_R; PinSocket_2x10_P2.54mm_Vertical_SMD
J13: POWER
L3: 47uH; L_Sunlord_MWSA1206S-470
Q1: IRLR8726; TO-252-2
R1: 3k; R_0402_1005Metric
R2, R3, R4: 1k; R_0402_1005Metric
RV1: 1k; Potentiometer_Bourns_TC33X_Vertical
U7: XL6019; TO-263-5_TabPin3

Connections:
3V7_P1: C18.1, C19.1, J13.1, L3.1, U7.4 (VIN)
GND_P1: C18.2, C19.2, C20.2, C21.2, C26.2, H5.1, H6.1, H7.1, H8.1, J13.2, Q1.3 (S), R2.2, R3.2, R4.2, U7.1 (GND)
GND_SERVO_P1: Q1.2 (D)
unnamed: D1.2 (A), L3.2, U7.3 (SW)
unnamed: R1.1, RV1.3
unnamed: R1.2, R2.1, U7.5 (FB)
SERVOA_P1: J4.4
SERVOB_P1: J4.6
SERVOC_P1: J4.8
SERVOD_P1: J4.10
SERVOEN_P1: J4.2, Q1.1 (G), R4.1
VDD_SERVO_P1: C20.1, C21.1, C26.1, D1.1 (K), R3.1, RV1.2

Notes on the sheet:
5V-6V POWER SUPPLY FOR SERVO

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
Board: 2 copper layers, 83 parts (0 on the bottom side), 53 nets, no tracks yet.

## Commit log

2024-11-16 Init
2024-11-16 Add readme
2024-11-16 Add license
2024-11-16 rev2.10
2024-11-18 v2.13
2024-11-19 v2.14
2024-11-19 ignore
2024-11-22 v2.16
2024-12-04 v2.20
2024-12-16 v2.22
2025-02-20 Pindefs added
2025-02-20 gitignore update
2025-02-20 Blockscheme update
2025-02-20 Photoes added
2025-03-26 readme update
2025-03-26 pindefs update
2025-04-03 adding photoes readme
2025-04-03 photo add
2025-04-23 topology photos added
2025-04-23 update topology
2025-04-25 dimentions added
2025-04-25 new blockscheme
2025-05-29 new software packet link
2025-07-18 revD manual
